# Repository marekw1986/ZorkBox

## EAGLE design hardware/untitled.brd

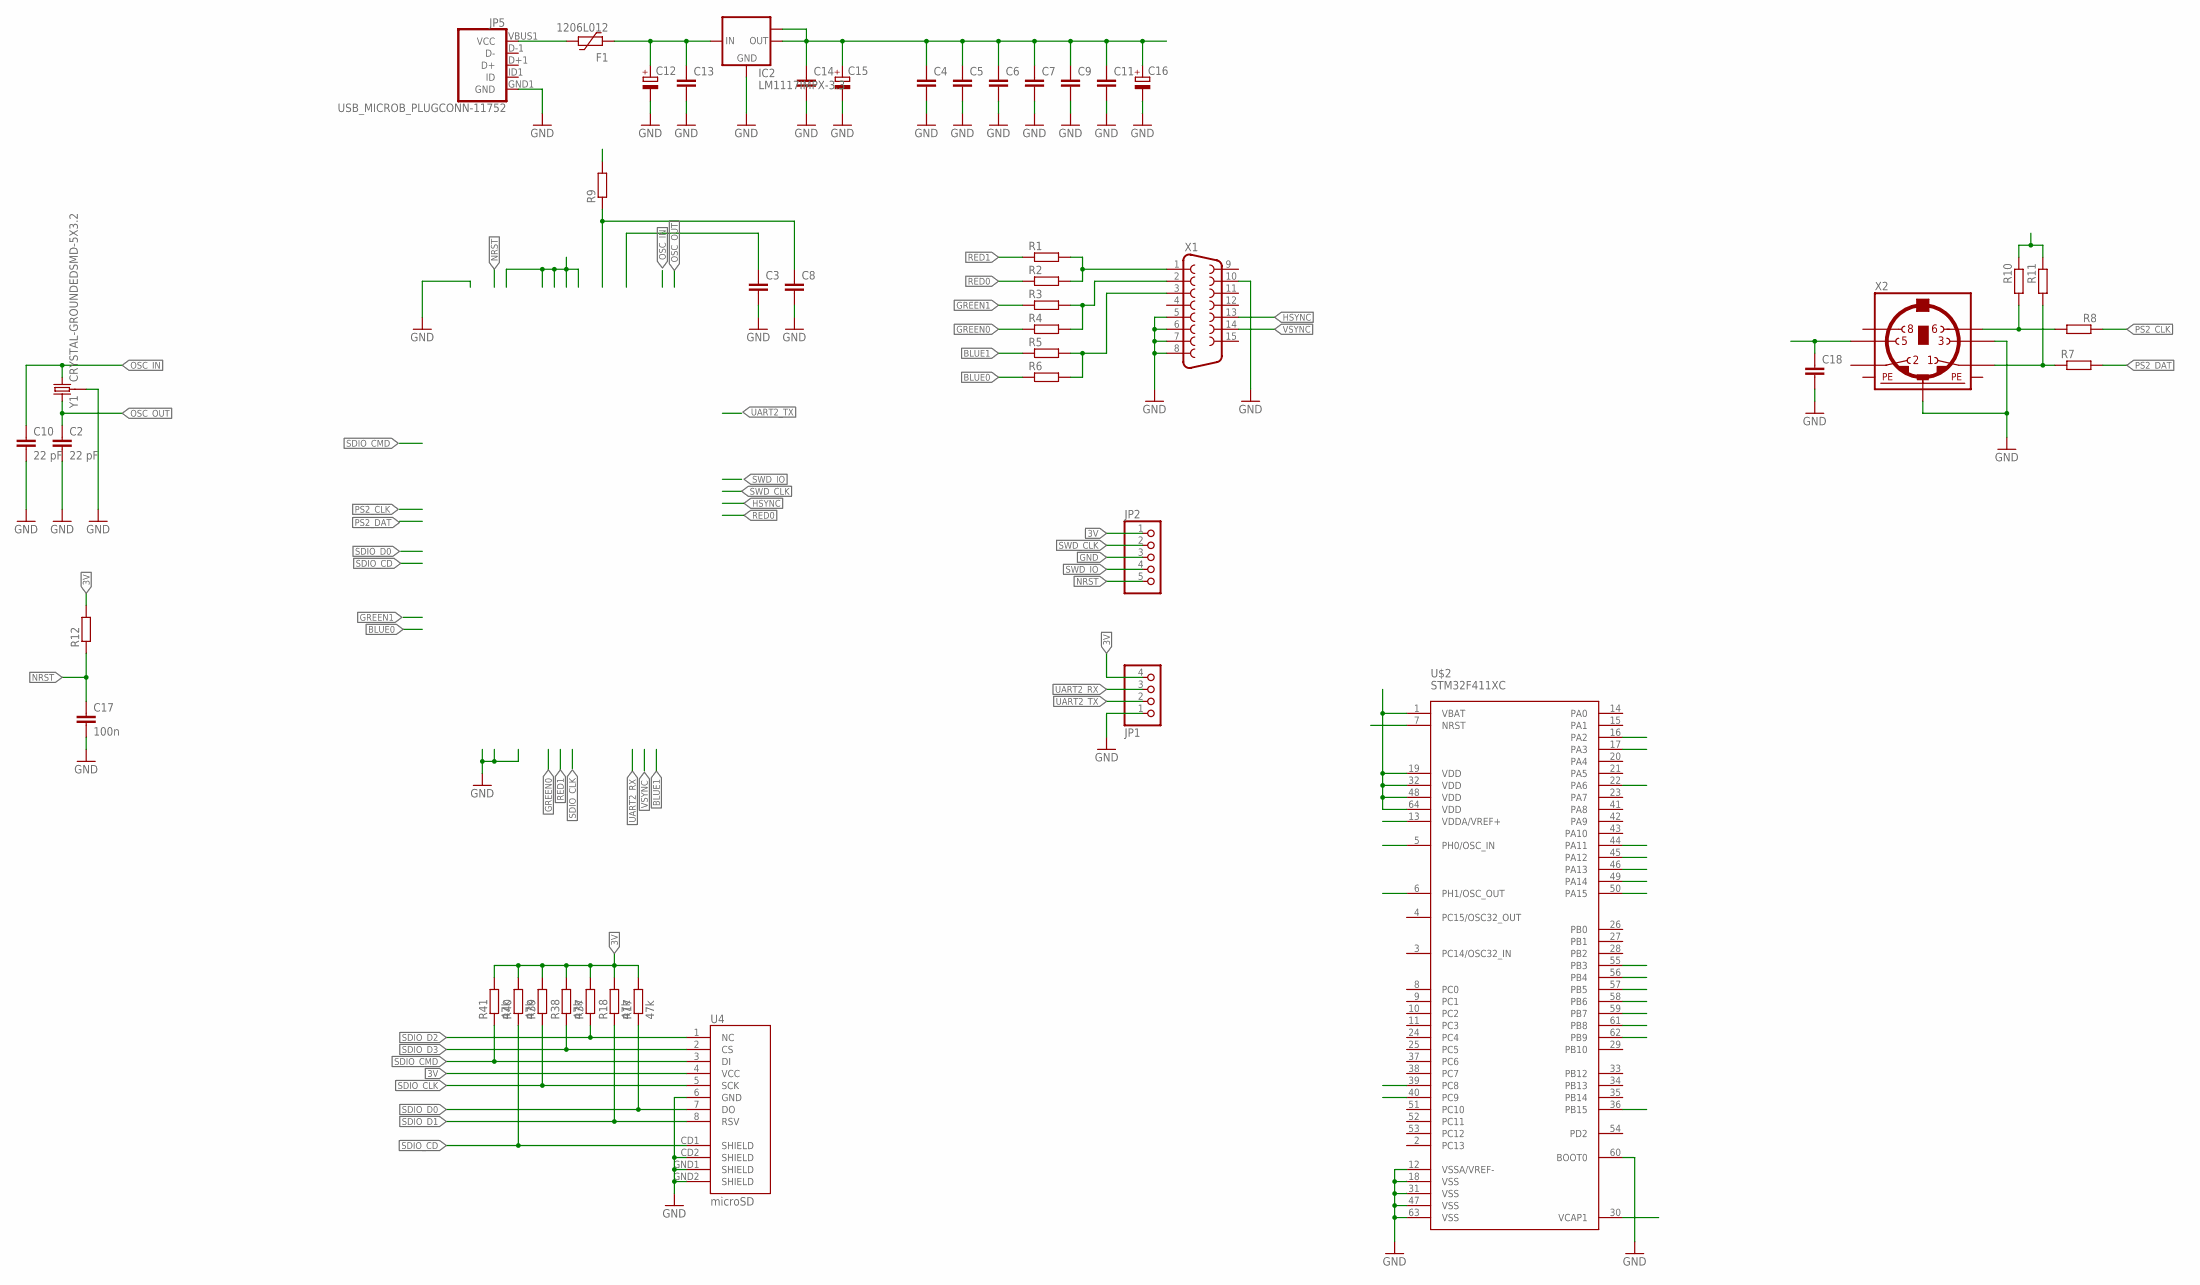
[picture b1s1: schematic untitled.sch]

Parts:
C2, C10: 22 pF; C0603
C3, C4, C5, C6, C7, C8, C9, C11, C13, C14, C18: C-EUC0603; C0603
C12, C15, C16: CPOL-EUSMCB; SMC_B
C17: 100n; C0603
F1: 1206L012; 1206L
IC2: LM1117IMPX-3.3; SOT223
JP1: PINHD-1X4; 1X04
JP2: PINHD-1X5; 1X05
JP5: USB_MICROB_PLUGCONN-11752; USB-B-MICRO-SMD_V03
R1, R2, R3, R4, R5, R6, R7, R8, R10, R11, R12, R39: R-EU_R0603; R0603
R9: R-EU_M0805; M0805
R17, R18, R40: 47k; R0603
R37: R-EU_R0402; R0402
R38, R41: 47k; R0402
U4: microSD; USD-SOCKET-PP
U$2: STM32F411XC; LQFP64
X1: F15HDH; HDF15H
X2: MINI_DIN_6; M_DIN6
Y1: CRYSTAL-GROUNDEDSMD-5X3.2; CRYSTAL-SMD-5X3.2-4PAD

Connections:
3V: C4.1, C5.1, C6.1, C7.1, C9.1, C11.1, C14.1, C15.+, C16.+, IC2.2 (OUT), IC2.TAB (OUT1), JP1.4, JP2.1, R9.2, R10.1, R11.1, R12.2, R17.2, R18.2, R37.2, R38.2, R39.2, R40.2, R41.2, U4.4 (VCC), U$2.1 (VBAT), U$2.19 (VDD), U$2.32 (VDD), U$2.48 (VDD), U$2.64 (VDD)
5V: C12.+, C13.1, C18.1, F1.2, IC2.3 (IN), X2.5
BLUE0: R6.1, U$2.59 (PB7)
BLUE1: R5.1, U$2.61 (PB8)
GND: C2.2, C3.2, C4.2, C5.2, C6.2, C7.2, C8.2, C9.2, C10.2, C11.2, C12.-, C13.2, C14.2, C15.-, C16.-, C17.2, C18.2, IC2.1 (GND), JP1.1, JP2.3, JP5.GND1 (GND), U4.6 (GND), U4.CD2 (SHIELD), U4.GND1 (SHIELD), U4.GND2 (SHIELD), U$2.12 (VSSA/VREF-), U$2.18 (VSS), U$2.31 (VSS), U$2.47 (VSS), U$2.60 (BOOT0), U$2.63 (VSS), X1.5, X1.6, X1.7, X1.8, X1.10, X2.3, X2.SH2 (PE2), Y1.2 (3), Y1.4 (3)
GREEN0: R4.1, U$2.57 (PB5)
GREEN1: R3.1, U$2.58 (PB6)
HSYNC: U$2.50 (PA15), X1.13
unnamed: R1.2, R2.2, X1.1
unnamed: R3.2, R4.2, X1.2
unnamed: R5.2, R6.2, X1.3
unnamed: R7.1, R11.2, X2.1
unnamed: R8.2, R10.2, X2.6
unnamed: C8.1, R9.1, U$2.13 (VDDA/VREF+)
unnamed: C3.1, U$2.30 (VCAP1)
unnamed: F1.1, JP5.VBUS1 (VCC)
NRST: C17.1, JP2.5, R12.1, U$2.7 (NRST)
OSC_IN: C10.1, U$2.5 (PH0/OSC_IN), Y1.1 (2)
OSC_OUT: C2.1, U$2.6 (PH1/OSC_OUT), Y1.3 (1)
PE1: X2.SH1 (PE1)
PE3: X2.SH3 (PE3)
PS2_CLK: R8.1, U$2.44 (PA11)
PS2_DAT: R7.2, U$2.45 (PA12)
RED0: R2.1, U$2.55 (PB3)
RED1: R1.1, U$2.56 (PB4)
SDIO_CD: R40.1, U4.CD1 (SHIELD), U$2.40 (PC9)
SDIO_CLK: R39.1, U4.5 (SCK), U$2.36 (PB15)
SDIO_CMD: R41.1, U4.3 (DI), U$2.22 (PA6)
SDIO_D0: R17.1, U4.7 (DO), U$2.39 (PC8)
SDIO_D1: R18.1, U4.8 (RSV)
SDIO_D2: R37.1, U4.1 (NC)
SDIO_D3: R38.1, U4.2 (CS)
SWD_CLK: JP2.2, U$2.49 (PA14)
SWD_IO: JP2.4, U$2.46 (PA13)
UART2_RX: JP1.3, U$2.17 (PA3)
UART2_TX: JP1.2, U$2.16 (PA2)
VSYNC: U$2.62 (PB9), X1.14

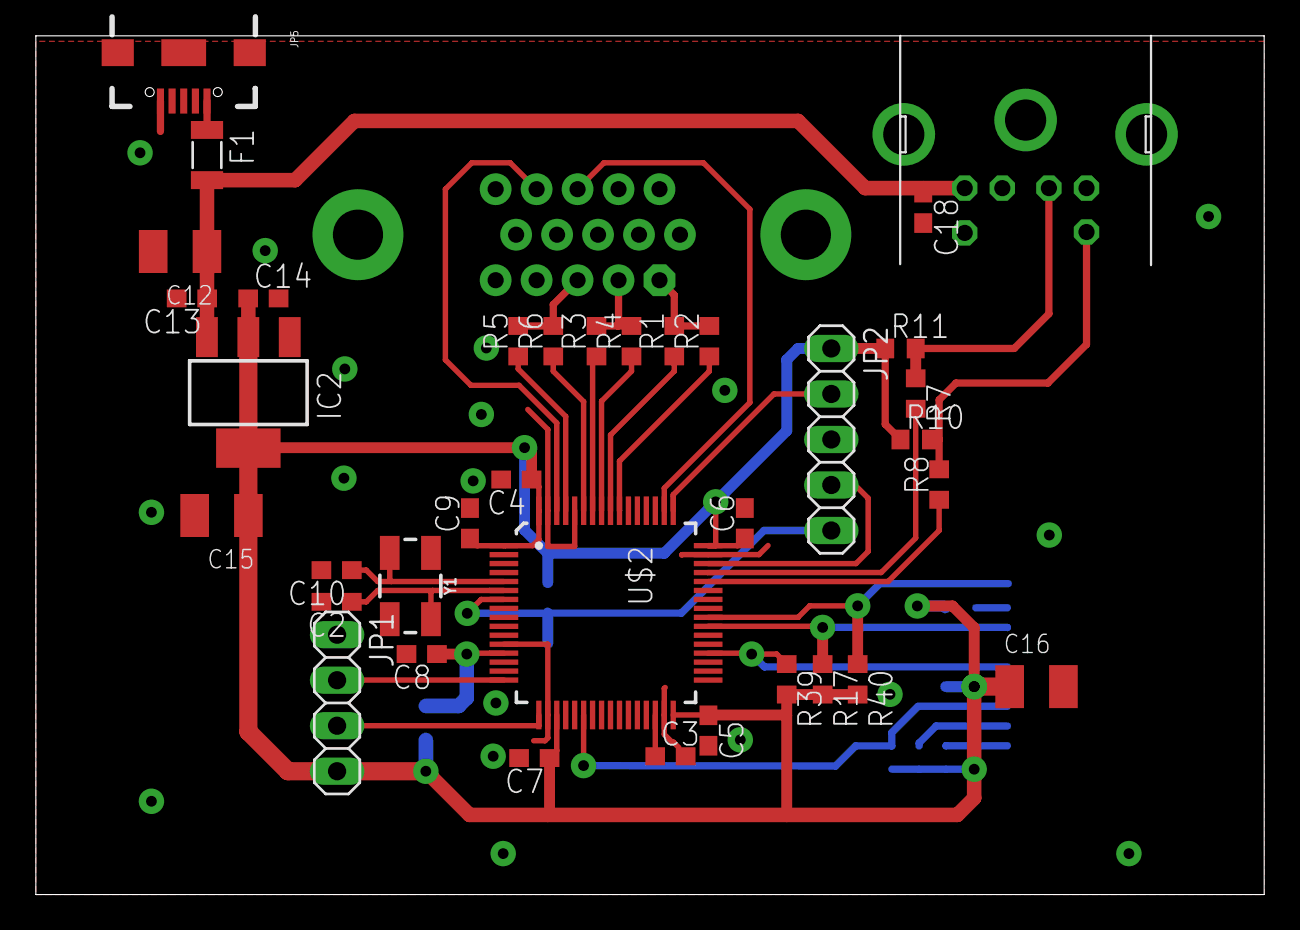
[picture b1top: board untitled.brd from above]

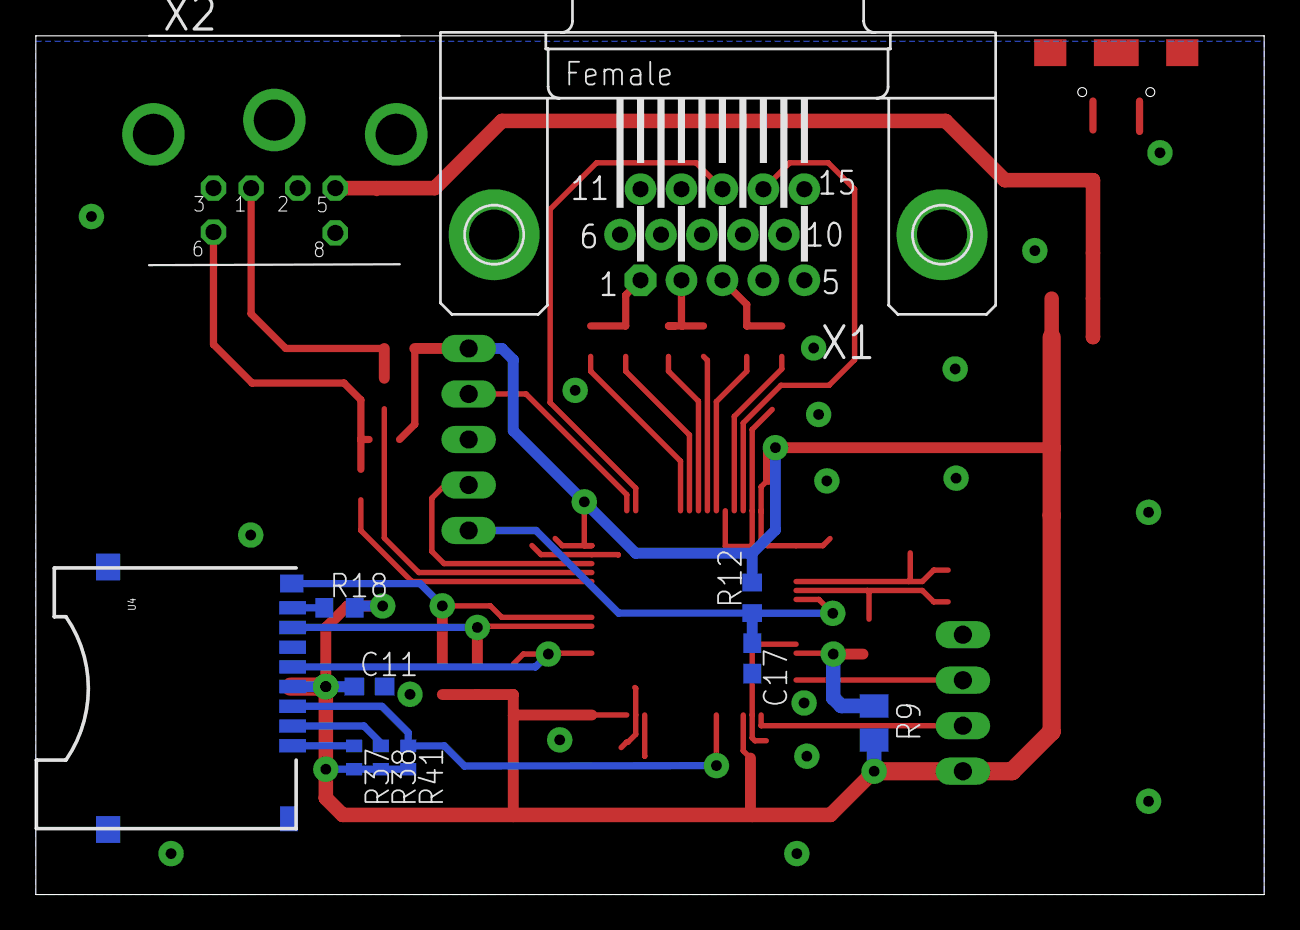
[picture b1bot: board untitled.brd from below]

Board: 2 copper layers, 68.6 x 47.9 mm, 46 parts (11 on the bottom side), 35 nets.

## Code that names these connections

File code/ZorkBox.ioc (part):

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Mcu.Name=STM32F411R(C-E)Tx
Mcu.Package=LQFP64
Mcu.UserName=STM32F411RCTx
PA11.GPIOParameters=GPIO_Label
PA11.GPIO_Label=PS2_CLK
PA11.Signal=GPXTI11
PA12.GPIOParameters=GPIO_Label
PA12.GPIO_Label=PS2_DATA
PA12.Signal=GPIO_Input
PA13.Mode=Serial_Wire
PA13.Signal=SYS_JTMS-SWDIO
PA14.Mode=Serial_Wire
PA14.Signal=SYS_JTCK-SWCLK
PA15.GPIOParameters=GPIO_Label
PA15.GPIO_Label=HSYNC
PA15.Signal=S_TIM2_CH1_ETR
PA2.Mode=Asynchronous
PA2.Signal=USART2_TX
PA3.Mode=Asynchronous
PA3.Signal=USART2_RX
PB3.Mode=TX_Only_Simplex_Unidirect_Master
PB3.Signal=SPI1_SCK
PB4.Signal=GPIO_Output
PB5.Mode=TX_Only_Simplex_Unidirect_Master
PB5.Signal=SPI1_MOSI
PB8.GPIOParameters=GPIO_Speed,GPIO_Label
PB8.GPIO_Label=BLUE1
PB8.GPIO_Speed=GPIO_SPEED_FREQ_VERY_HIGH
PB8.Signal=GPIO_Output
PB9.GPIOParameters=GPIO_Label
PB9.GPIO_Label=VSYNC
PB9.Signal=S_TIM4_CH4
PC9.GPIOParameters=GPIO_Label
PC9.GPIO_Label=SDIO_CD
PC9.Signal=GPIO_Input
PH0\ -\ OSC_IN.Mode=HSE-External-Oscillator
PH0\ -\ OSC_IN.Signal=RCC_OSC_IN
PH1\ -\ OSC_OUT.Mode=HSE-External-Oscillator
PH1\ -\ OSC_OUT.Signal=RCC_OSC_OUT
RCC.HSE_VALUE=8000000
RCC.SYSCLKFreq_VALUE=100000000
RCC.SYSCLKSource=RCC_SYSCLKSOURCE_PLLCLK
board=custom

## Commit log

2026-03-05 PCB added
2026-03-05 Code added
2026-03-05 Reset fix
2026-03-05 More GND vias
2026-03-05 Capacitor at PS/2 socket
2026-03-05 PS/2 power width increased
2026-03-06 Proper MCU footprint used
2026-03-06 Capacitor removed
2026-03-06 Minor adjustment
2026-03-09 printf connected to UART2
2026-03-11 Configuration fix
2026-03-11 Zork code added. Comiles now, with few warnings. Requires integration with hardware. Low level Arduino code commented out.
2026-03-11 Zork disk operations partially implemented
2026-03-11 Zork calls added to main.c
2026-03-12 Open file rewritten to FatFS
2026-03-12 Input redirected to UART2
2026-03-12 Output functions linked to uart2
2026-03-12 Zork works in terminal
2026-03-12 PS/2 library added
2026-03-13 Using RAM buffer for Zork dynamic data instead of tmp file on SD card
2026-03-14 Typo fixed
2026-03-14 VGA driver (work in progress)
2026-03-14 RGB pins reconfigured to very high speed
2026-03-14 System clock reconfigured to 100 MHz in order to ger 25 MHz for VGA
2026-03-14 Experiment with HSYNC generation
2026-03-17 Basic VGA funcionality. Something visible on screen...
2026-03-18 Color related definitions removed from VGA, init added, only visible lines transmitted by SPI
2026-03-20 VGA experiments. OC driven vertical back porch. No flicker.
2026-03-22 Fonts added
2026-03-22 Implementation of actual function filling scanline
2026-03-22 Experiments with DMA SPI scanline
2026-03-22 TIM4 OC initialization fix
2026-03-22 Old fill_scanline function removed
2026-03-23 Implementation of own SPI DMA functions
2026-03-23 Optimization level O3
2026-03-24 Character generator works
2026-03-24 Minor cleanup
2026-03-24 Optimization
2026-03-25 Basic terminal implemented
2026-03-25 Priorities changed, blinking cursor
2026-03-26 Cursor blinking independent from HAL milliseconds timer
2026-03-29 Not needed code removed
2026-03-29 Minor change
2026-03-29 VGA Optimization
2026-04-19 Parts of HAL dependent code removed from vga.c
2026-04-19 Another parts of HAL related code removed
2026-04-19 DMA addresses only set once at init
2026-04-19 More HAL related code removed from vga.c
2026-04-20 HAL dependencies removed from HSYNC/VSYNC timers
2026-04-20 Optimizations and adjustments
2026-04-20 Minor improvements
2026-04-20 Old fill scanline restored
2026-04-20 DMA2_Stream2_IRQHandler moved to vga.c
2026-06-04 FreeRTOS removed from project
2026-06-04 Cleanup
2026-06-04 Minor fix
2026-06-07 P2/2 keyboard configured and tested
2026-06-07 VGA code prepared for buffer updating in main loop
2026-06-07 scanline updated in main loop
2026-06-07 Frame removed
2026-06-08 Blinking cursor added again
2026-06-08 Experimental changes in zork engine
2026-06-08 Double buffering updated
2026-06-09 Working VGA and PS/2
2026-06-10 Zork refactored for cooperative mode
2026-06-10 Backspace added
2026-06-10 Cursor leftover at end fix
2026-06-10 Minor changes
2026-06-10 ZORK1.DAT hardcoded
2026-06-12 VGA interrupt functions stored in RAM
2026-06-14 Zork uses game data from flash
2026-06-14 DMA removed from SDIO due to conflicts with VGA
2026-06-14 Terminal problem fixed
2026-06-14 Blinking cursor restored, minor cleanup
2026-06-14 FatFS removed, zork restarts on quit command
2026-06-15 vga_puts() added, print added at save/restore attempt
2026-06-15 Eliza code added
2026-06-15 Eliza code fix
2026-06-21 Watchdog added
2026-06-21 Eliza reset
2026-06-21 Missing files added

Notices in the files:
parts and their libraries:
SparkFun-Connectors: Licensing: Creative Commons ShareAlike 4.0 International - https://creativecommons.org/licenses/by-sa/4.0
